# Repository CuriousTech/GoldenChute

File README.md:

# GoldenChute
GoldenMate UPS monitor and Windows shutdown software  
  
This is a simple modification for the GoldeMate UPS to access the information displayed as well as safely shut a Windows PC down before the battery runs down. One of the most important features of a UPS.  

The left is the web page for remote access. The other windows are the Windows app (different sizes).  
  
This mod requires opening the case of the UPS and plugging in a small board inline with the front display. It's a segmented display with SPI interface, so the ESP32 decodes all the segment bits and translates them to something usable. The data is only sent to the display for 60 seconds when the power button is short-pressed, so this also simulates the button (in parallel). The 5V power for the ESP32 needs to be external since the display 5V is only on when the display is powered, and may not support the current requirement, so run a USB cable to the rear panel and cut a small notch so the case can slide back on, and connect to PC or USB power supply (powered by the UPS, so it's powered on battery).  
  
I beleve the first model had a push-on/push-off button and the display stayed on. For that model, all you need is the PCB, ESP32, and 7 pin connectors. Leave out the solid state relay, R2 and 2 pin connectors.  
  
**Parts needed:**  
-  [PCB r4](https://oshpark.com/shared_projects/ARcXjJj3)  Moved the DI trace to fix RF issues with a new module, and removed ground fill around it as well.  
-  [ESP32-C3-super mini](https://www.aliexpress.us/item/3256807353297685.html), or [ESP32-S3-super mini](https://www.aliexpress.us/item/3256809251035142.html) for USB-HID support (native Windows, NUT, etc.)  
-  2x AQY282S (SSR)  I used this one because it's cheap and currently well stocked.  
-  R1 2x 470 ohm 0805 resistor  
-  M & F [JST-XH](https://www.aliexpress.us/item/3256807274583113.html) (This one has wires to place it closer to the side for better signal) 7P 2.54mm, or 7P 0.1" pinheader  
-  2P 2.54mm/0.1" connector M  
-  2P 2.54mm/0.1" connector F + 2 wires (3-4 inches) Note: The button is non-polarized (The AliExpress above didn't fit the 2 pin) Dupont will work if nothing else.  
-  (Optional) 1x 18650 cell and [holder](https://www.aliexpress.us/item/3256808726723157.html) for battery power on the ESP32. Solder the wires on the back of the ESP32 first.  
-  r5 board: 3x BSS138 (MOSFET), 3x 10K resistors, and another AQY282S + 470 resistor. This is still an untested board. The addition of the SSR is because the front button is DPST. One side is for the BMS (display control). The other side is for the UPS (powering on and beeper mute). Some models have separate buttons for this function, and may have different input timings.  

Remove the 2 screws under each rubber foot. Slide the cover off (to the front).  Remove the 6 screws around the front panel.  
  
The female XHB (XH works well, and a plain female pinheader actually holds well if you can't find XH/B) connector needs pins or wire lead clippings crimped to make it solder to a PCB. I used male pinheader pins. Install the 2-pin connector and wires before the ESP32 for ease.  

Cut a notch in the rear panel to fit the USB cable.  
  
**Arduino:**  
Settings for router SSID and SSID password are in Config.h, as well as the remote password for web control. If they aren't set or the SSID changes, EspTouch can be used.  
Compiling the code should be easy. Most information is in UPS.ino, like where to get the libraries needed, and settings for the ESP32-C3-super mini such as enabling CDC on boot (for serial output).  
The S3 must be set to USB-OTG + CDC On Boot for the serial and USP-HID option.  
There's code in UPS.ino to setup the initialDate, lastCycleDate, Cycles and percent to be used once, and commented out if desired.  

The ESP32-S3 super mini is mostly pin compatible, and has HID support for UPS emulation. It has 2 more pins (1 per side) that just overhang on the PCB. The current GPIO pins in the code for the C3 are incorrect for the r3 board. Just 1 pin is different. There are likely different models of the S3 also. Just make sure GND is pin 2.  
  
**Web page:**  
The HIBERNATE and SHUTDOWN buttons send a message to the Goldenmate app to start the shutdown or hibernate process.  
The POWER OFF button will hold the power button for 5 seconds to shut the UPS off. This will cut power to everything, including the ESP32 most likely, if no battery is used.  
RESET DISP causes a timeout in the display restart timer. When the USP returns to AC power, once in a while the display malfunctions, but the data is still good. This just fixes it.  
BEEPING / SILENT toggles to enable a button tap at the start of backup power, disabling the beeps.  
Shutoff Watt Threshold prevents the delayed shutoff from operating until the watts out drops below the set value.  
HID Warn % is what Windows uses to pop up a warning.  
HID shutdown % is what Windows uses to shutdown when the battery level reaches that value. Set the warning above the shutdown. These are overridden by settings in Windows, though, so probably not useful.  
PPKWH (price per killowatt hour) is used for, well, calcuating cost.  
password needs to be the same as what's in Config.h and needs to be set to allow any input (button presses or value changes). You can leave it blank any other time.  
  
**Windows app:**  
Extract the exe and move it to somewhere like C:\Goldenmate.  The startup folder symbolic link will auto-generate to this path.  
Clicking on the top-right corner of the app will hide it.  
Right-click for context menu (settings, quit, clear log/chart)  
The outage and daily WH log (top right area, hidden when small) is blank until an entry is created.  Entries are comma delimited lines saved in a file in the local exe folder, named ups_log.txt (or ups_log1.txt for the 2nd instance...).  
  
**Settings:**  
Right-click in the window, or go to the tray, and right click the icon for the menu. Select "Settings" and enter the IP address of the ESP32 device in the format "192.168.xxx.xxx" which you can find in the Arduino IDE ports, named UPS (192.168.xxx.xxx). Up to 8 clients can be connected at once. Your router should also be on UPS when using this method.  
If it connects, there should be a small red circle in the top left of the app. This will blink when data is received. Serial is the same.  
COM Port (Note: using serial will cause the ESP32 to reset every time the app exits or another app accesses the COM port, which loses WH history and may get off track if charging).  
The radio buttons allow selecting either COM or websocket.  
 Note: When using HID, the Windows app can still use serial or connect to the IP address, but be careful of the HID shutdown % along with the app shutdown %. The app should be set higher, and HID can be fallback if it's not running for any reason.  
Percent to shut down: Active (red bars left of battery in the main display and tray icon) and Inactive (right red bars) depends on whether the monitor is in standby. The depth of discharge (D.O.D.) determines the impact on health. When inactive, it should shut down at 70% for best health. When active, more time can be allowed for manual shutdown. The % is just the bar levels, not actual percent (which could possibly be inaccurate). There is a 10 second delay when it reaches the desired %, then it will shut down or hibernate/hibrid-sleep if that is set up properly and doesn't fail, otherwise it will shut down.  
Note: Hibrid-sleep can wake immediately by odd USB devices if not set up properly. It should be tested before use. It will also slowly drain the battery over time.  
Skip seconds: 0 will add data to the chart every second (total 24 hours). 1 would be 48 hours, but records peak values of 2 seconds.  
Alerts cause the window to popup and show a text box such as "Serial timeout/in use" or WebSocket disconnected" with annoying sound.  
Power off after [30] seconds: Will turn the UPS power off (cutting power to everything on it) the delayed time (15 secs to 60 mins) after the PC begins shutdown/hibernate, and also waits for the watts out to drop below the shutoff watt threshold setting on the webpage.  
 Note:The ESP will also lose power, so there's no way to remotely power it back on.  
Hide after start causes the window to hide 4 seconds after startup.

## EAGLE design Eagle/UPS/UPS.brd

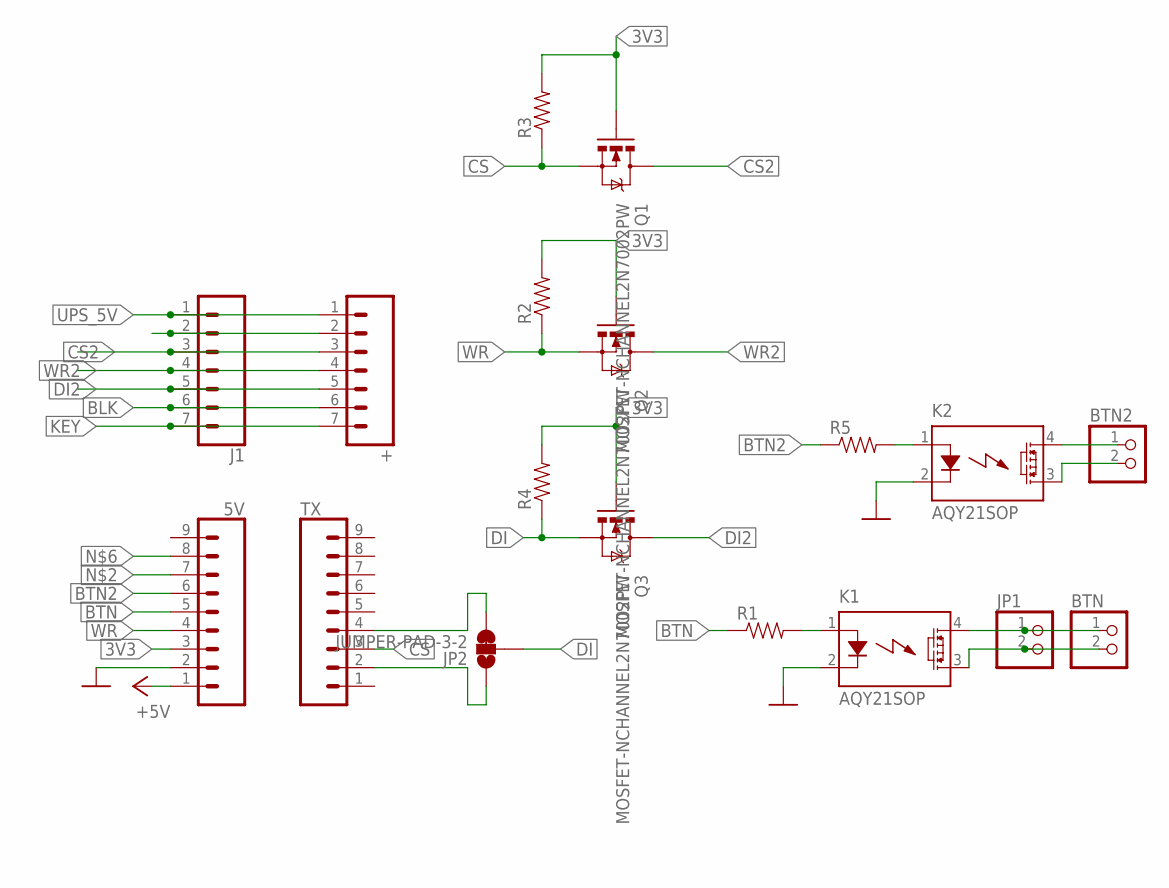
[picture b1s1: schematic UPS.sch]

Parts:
5V: CONN_09; 1X09
+: CONN_07; 1X07
BTN, BTN2: PINHD-1X2; 1X02
J1: CONN_07; 1X07
JP1: PINHD-1X2; 1X02
JP2: JUMPER-PAD-3-2; PAD-JUMPER-3-2OF3_NC_BY_TRACE_YES_SILK_FULL_BOX
K1, K2: AQY21SOP; SOP04
Q1, Q2, Q3: MOSFET-NCHANNEL2N7002PW; SOT323
R1, R2, R3, R4, R5: RESISTOR0805-RES; 0805
TX: CONN_09; 1X09

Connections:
3V3: 5V.3, Q1.1 (G), Q2.1 (G), Q3.1 (G), R2.2, R3.2, R4.2
+5V: 5V.1
BLK: +.6, J1.6
BTN: 5V.5, R1.1
BTN2: 5V.6, R5.1
CS: Q1.2 (S), R3.1, TX.3
CS2: +.3, J1.3, Q1.3 (D)
DI: JP2.2, Q3.2 (S), R4.1
DI2: +.5, J1.5, Q3.3 (D)
GND: 5V.2, K1.2 (K), K2.2 (K)
KEY: +.7, J1.7
unnamed: BTN.1, JP1.1, K1.4 (DS1)
unnamed: BTN.2, JP1.2, K1.3 (DS2)
unnamed: K1.1 (A), R1.2
unnamed: JP2.3, TX.4
unnamed: JP2.1, TX.2
unnamed: BTN2.1, K2.4 (DS1)
unnamed: BTN2.2, K2.3 (DS2)
unnamed: K2.1 (A), R5.2
UPSGND: +.2, J1.2
UPS_5V: +.1, J1.1
WR: 5V.4, Q2.2 (S), R2.1
WR2: +.4, J1.4, Q2.3 (D)

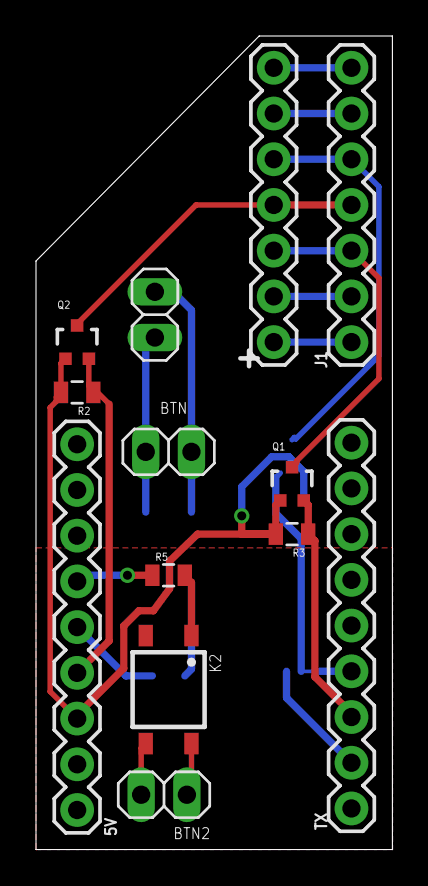
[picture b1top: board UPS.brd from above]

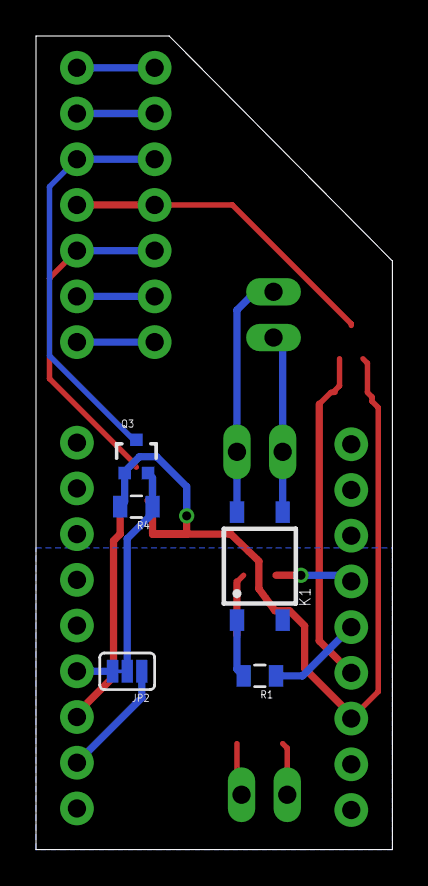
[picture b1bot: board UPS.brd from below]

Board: 2 copper layers, 19.8 x 45.2 mm, 18 parts (5 on the bottom side), 22 nets.

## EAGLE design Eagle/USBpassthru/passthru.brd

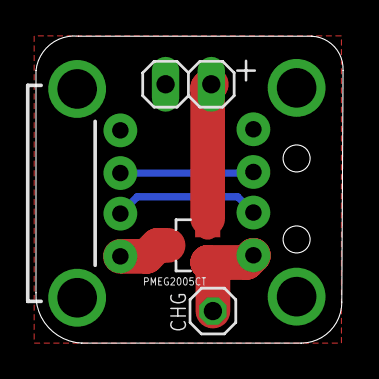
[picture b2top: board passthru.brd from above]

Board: 2 copper layers, 17.1 x 17.1 mm, 5 parts (1 on the bottom side), 6 nets.

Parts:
+: plug; 1X02
CHG: 1X01
IN: USB-A; USB-A-H
OUT: USB-A; USB-A-H
PMEG2005CT: BAT54C; SOT23

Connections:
+5V: CHG.1, IN.VBUS, PMEG2005CT.1
D+: IN.D+, OUT.D+
D-: IN.D-, OUT.D-
GND: +.2, IN.GND, IN.GND2, IN.GND3, OUT.GND, OUT.GND2, OUT.GND3
unnamed: OUT.VBUS, PMEG2005CT.3
unnamed: +.1, PMEG2005CT.2

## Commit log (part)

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2025-07-07 Remove unneeded includes
2025-07-07 Auto-reconnect added
2025-07-07 PC connection status
2025-07-08 Added serial rx
2025-07-08 Added serial tx
2025-07-08 Added cheaper SSR options
2025-07-08 Bitpacked the data payload
2025-07-08 Added shutdown/hibernate commands to serial
2025-07-09 Removed timelib and udptime dependency
2025-07-10 Added serial format request
2025-07-10 Added serial format request and outage logging
2025-07-10 Comm timeout error popups, dark theme log list
2025-07-11 Found correct connectors
2025-07-12 typo fix
2025-07-13 Chart slide/zoom fixes
2025-07-13 Segment validity checks
2025-07-13 Unhide and beeping if U## error
2025-07-13 Expects just 4 bytes for serial ID
2025-07-15 Added battery level to chart
2025-07-17 Added 1000/1500VA ID for future use
2025-07-17 Added 1000/1500VA ID
2025-07-17 Changed bin format, added default text mode
2025-07-17 Changed bin format
2025-07-17 About that older model
2025-07-21 Connector problems
2025-07-23 Improving info. XH or XHB option. Corrected resistor value
2025-07-27 Probably the skip seconds added
2025-07-28 Forgot the pinmode
2025-07-29 Right-click tile for settings
2025-07-31 Clear button, context menu
2025-07-31 Fewer ws sends
2025-08-02 Bit defs for data, smaller ISR code
2025-08-05 Link to new PCB
2025-08-05 Removed images of rev0, new will be flipped
2025-08-06 tzo should be signed
2025-08-09 Tiny mode, adjustable colors
2025-08-10 Error code text
2025-08-10 Error code text added
2025-08-12 Est batt time, batt health setting
2025-08-14 Update for code changes
2025-08-14 Update for battery levels
2025-08-14 Fixed Incorrect battery levels
2025-08-14 Settings fixed for new levels
2025-08-14 Decided on even numbers for levels
2025-08-14 Made levels even.. 5,10,20...
2025-08-14 Back to 9,19,29...
2025-08-14 Back to odd numbers for accuracy
2025-08-14 Back to odd numbers
2025-08-14 copy mistake
2025-08-15 Changed binary data format
2025-08-15 Using percent from ESP
2025-08-15 Added percent to binary
2025-08-16 Battery level 1% resolution
2025-08-20 Changed bin data format again for alignment
2025-08-20 Change bin data format
2025-08-20 Bad memset
2025-08-20 More serial diag/reconnects
2025-08-22 More compact option
2025-08-23 Component placement pics added
2025-08-23 Rev 2 PCB update
2025-08-23 Changed pin assignments for new design
2025-08-25 Clear chart works, better conn indicator
2025-08-25 Fewer fails for data convert
2025-08-26 Small visual changes
2025-08-26 New UI stuff
2025-08-26 UI changes, colors, positions
2025-08-26 Multi-bin clients, fix for full charge reached
2025-08-27 Better filter in case display is off
2025-08-28 More comm error checking
2025-08-28 "No data" check
2025-08-28 Added comment
2025-08-28 Error msg if no data
2025-08-29 Batt level / percent rework
2025-08-30 Adjustments to width
2025-08-30 More percent tweaks
2025-08-31 Bar level changes
2025-08-31 Added display restart button
2025-08-31 Change battery bar levels, display restart
2025-09-01 Back to old bar values
2025-09-01 Old bar levels were right. Fudging the percent calc to look right
2025-09-01 Potential issues
2025-09-03 White on black colors
2025-09-05 Disconnect/reconnect fix
2025-09-05 Added daily usage, batt full log
2025-09-08 Power usage moved to ESP32
2025-09-08 Added power usage graph
2025-09-08 removed tz, added ppkwh
2025-09-08 Used hard coded TZ, added power usage
2025-09-10 Wrong dir
2025-09-12 min/max additions
2025-09-12 Better percent calculations
2025-09-16 One more websocket reconnect on failure
2025-09-20 Adjusted Wh for models
2025-09-20 Wider bar area
2025-09-20 Added Wh for 1000VA/600W
2025-09-23 Changed bin format, interrupt priority
2025-09-26 Changed some wording
2025-09-26 Shutdown level goes to 0% for off
2025-10-01 Changed bin format again
2025-10-01 Data saved for batt health
2025-10-04 Added HID powerdev if ESP32S3
2025-10-05 Wrong link to PCB, removed r2
2025-10-07 Cycle reminder
2025-10-07 last cycle date
2025-10-07 single call for 2 things
2025-10-07 Added 90 day cycle reminder
2025-10-07 Update for changes
2025-10-07 Fixed a bad Y pos
2025-10-07 Changed 97% values to 98%
2025-10-11 Removed health adjust, uses UPS data
2025-10-13 Display health and cycles
2025-10-13 Added health calc
2025-10-14 Forgot it's not self powered
2025-10-17 Changed last cycle date to accumulated 100%
2025-10-17 Added dual shutdown modes
2025-10-19 Added HID/serial option for S3
2025-10-19 Removed a debug line
2025-10-20 Added ESP32-S3
2025-10-24 Small aesthetic changes
2025-10-26 Found memory leak
2025-10-30 Added power button
2025-10-30 Removed init
2025-10-30 size offset was wrong
2025-10-30 moved funcs to private
2025-10-30 Removed unused info
2025-10-30 Fixed health calc, added power button, initialdate setting
2025-10-30 Forgot what I was doing
2025-10-30 Forgot to pass a number
2025-11-01 Bug in the "needCycle" indicator
2025-11-01 "needCycle" bug
2025-11-01 Fixed "needCycle" blinker
2025-11-02 HID updates were in the wrong place
2025-11-02 Wording
2025-11-04 Changed tray icon a bit
2025-11-10 Added time remaining
2025-11-10 Added more feature support
2025-11-10 Added HID features and time remain
2025-11-12 Added delayed power off
2025-11-12 Fixed poweroff value
2025-11-12 Added peak wh
2025-11-13 Cancellable shutoff
2025-11-14 Shutoff cancels of not on battery
2025-11-17 Proper working dir for symlink
2025-11-17 Corrected timer under 1 hour
2025-11-17 More active time remaining
2025-11-18 Again with the time remaining
2025-11-18 Dumb math error
2025-11-21 Added check for noData to stop shutdown
2025-11-25 Sends close message to UPS
2025-11-25 Saves usage on PC app shutdown
2025-11-26 Fresh typo
2025-12-01 Fixed data save on shutdown
2025-12-13 Fixed cycle add up
2025-12-15 Fixed potential long button press at start
2025-12-20 Changing from preferences to SPIFFS files for persistence
2025-12-20 Added 30 day totals
2025-12-29 Monthly chart and HID shutdown level adjust
2025-12-29 wrong size for dailywh file
2025-12-29 HID values added
2025-12-29 Adjustable values added
2025-12-29 HID value adjusts
2025-12-30 Wrong year
2025-12-30 Made month days better
2026-01-02 Turns out I care about that day thing
2026-01-02 Write bug
2026-01-06 percent usage fix
2026-01-08 A bit better battery bar reading
2026-01-08 Changed binary packet format
2026-01-08 Using raw battery segments
2026-01-08 Changed to 1/10th cents
2026-01-08 Changed battery levels to even, bin format, removed peakchargewh
2026-01-09 C3 compliable again
2026-01-11 Sends a close message when exiting
2026-01-11 Timer display and cancel power off
2026-01-11 Support for web shutoff timer, more connect status
2026-01-12 Should have kept the array 32 bit
2026-01-15 Changed hourly data format
2026-01-15 Cleaner hourly data
2026-01-24 Fixed possible false FULL event
2026-02-04 Shutoff watt threshold
2026-02-04 typo
2026-02-04 divide by 0 bug
2026-02-04 Added heatsink
2026-02-05 Update README.md
    New PCB rev
2026-02-12 Removed r3 link
2026-02-20 Missed a variable change, reconnect delay
2026-02-21 Wrong link to PCB (sorry)
2026-02-25 Lowest TX power to reduce heat
2026-03-04 EspTouch improvement
2026-03-14 Saves prefs properly on shutdown
2026-03-16 One more serial timeout check
2026-03-22 Changed JST-XH connectors link
2026-03-22 TX power level control
2026-04-25 DEL key to delete a log entry
2026-05-05 Testing
2026-05-05 Testing 2
2026-05-09 Changed default IP address to ups.local
2026-05-31 Adjusted widths and relative websocket path
    Updated styling and script elements in the HTML structure. Modified WebSocket initialization and power level display.
2026-06-21 New popup error messages
2026-06-22 Add silence function
2026-06-22 Added silent/beeping option when on battery.
    Added pin definitions, added new configuration option, and modified several logic conditions for better functionality.
2026-06-22 Revise alert text and power off settings in README
    Updated alert description and clarified power off behavior.

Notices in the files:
parts and their libraries:
SparkFun-Connectors: Licensing: Creative Commons ShareAlike 4.0 International - https://creativecommons.org/licenses/by-sa/4.0
